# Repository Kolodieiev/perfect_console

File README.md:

Проєкт “Ідеальна консоль” це спроба створити універсальну електронну плату, для комфортного програмування на її основі різноманітних електронних пристроїв, таких як ігрові консолі, програвачі музики, пульти керування тощо.
Завдяки продуктивному мікроконтролеру ESP32S3 N16R8 плата може виконувати купу завдань та обчислень, а наявність 8 мб оперативної та 16 мб постійної пам'яті, забезпечує достатньо місця для реалізації досить об’ємних проєктів прошивок, в тому числі з використанням графіки. 

<br>

#### Прошивка
В репозиторії, крім файлів проєкту електронної плати, містяться повністю відкриті базові прошивки, написані мовою C++, для обох мікроконтролерів. Прошивка для ESP32S3 базується на основі фреймворку Pixeler, та містить багато прикладів побудови графічного інтерфейсу різної складності. 
До їх списку входять різні види меню, графічний інтерфейс для сканування та підключення до WiFi точки доступу, файловий менеджер, mp3-плеєр, вікна з різними видами налаштувань, приклади 2D-ігор на кастомному ігровому рушії та інші.

Скриншоти з прошивки:<br>

<br>

<br>
Демонстрація можливостей ігрового рушія(зібрано в портованій версії для ПК):
<br>

<br>
Більше скриншотів можна знайти в [Screenshots](resources/images/screenshot)
<br>

#### Для кого
Проєкт розрахований на користувачів, які хочуть навчитися виготовляти або замовляти виготовлення електронних плат, збирати їх по схемі та програмувати мікроконтролери. Також він підійде досвідченим розробникам, яким просто цікаво програмувати залізо у вільний час та вивчати щось нове для себе. 
Для збірки проєкту необхідно мати досвід пайки середнього або вище рівня та відповідні інструменти.

<br>

#### Модульність
Головна особливість плати полягає в тому, що користувач може самостійно обрати, який модуль йому використовувати для своїх задач. На платі передбачено місця тільки для основних компонентів, або таких, які складно закріпити в корпусі окремо, все інше необхідно самостійно обирати з огляду на власні потреби та можливості.
<br>
<br>
[Фото зібраних плат](resources/images/pcb)

<br>

#### Корпус
Розробка корпусу для виготовлення на 3D-принтері не планується в межах даного проєкту. Користувач повинен самостійно спроектувати корпус для свого пристрою в залежності від використаних модулів. 

<br>

#### Мікроконтролер
Для забезпечення функціонування плати використовується два мікроконтролера - далі МК, ESP32S3 та CH32V006E8R6. Ці МК обрано через дуже хороше співвідношення ціна/можливості та значну кількість GPIO. Очікується, що перший МК буде мозком пристрою, який виконуватиме основну прошивку, а другий - допоміжний, що виконуватиме роль мікросхеми розширення, завдяки якій вивільняються 11 пінів основного МК. Мікроконтролери можуть спілкуватися один з одним по шині I2C. Для підтримки рівноправного двостороннього зв'язку додано окрему лінію між МК, яка може бути використана для генерації переривань.

<br>

#### GPIO
До однієї з двох шин SPI на ESP32 приєднано роз’єм карти пам’яті MicroSD. Усі інші незадіяні виводи цього МК виведено на штирьові роз’єми та контактні площадки. Усього доступно вільних пінів 19 + шина I2C + UART. Усі вільні виводи ESP32 згруповано на штирьових роз’ємах таким чином, щоб до них можна було підключити з допомогою шлейфів будь-який популярний SPI-дисплей, модуль звуку, який керується по I2S протоколу, цифровий мікрофон та UART-версію модулів LoRa. До кожної групи роз’ємів додано піни живлення, які вмикаються польовими транзисторами. В кастомній прошивці до цих роз’ємів можуть бути підключені будь-які інші модулі на розсуд користувача.

Частина виводів(п’ять) CH32 підключені до ключів керування живленням. Усі інші піни також виведені на штирьові роз’єми. У стандартній конфігурації до цих пінів очікується підключення кнопки живлення, кнопки PTT, ліній UART, програматора, та 8 кнопок керування, 6 з яких, можуть бути налаштовані як сенсорні. 

В будь-якій користувацькій конфігурації обов’язковою є тільки кнопка живлення. Усі інші вільні виводи мікроконтролерів можуть бути налаштовані, відповідно до їх документації, на інші задачі. Окрім того, за особливої необхідності, можуть бути звільнені додаткові 4 піна CH32, які підключені до затворів ключів живлення в кожній групі штирьових роз’ємів.

<br>

#### Живлення
Очікується, що плата “Ідеальної консолі” буде використовуватися саме в автономному варіанті з використанням високоємнісного акумулятора або збірки акумуляторів. Проте з деякими незначними модифікаціями можливе її використання виключно в стаціонарному варіанті, наприклад, для навчання або відлагодження. На платі передбачено місця для штирьових роз’ємів, до яких можна підключити будь-який USB роз’єм, та будь-який понижуючий DC-DC перетворювач. Також окремо виведено роз’єм з підсиленими доріжками для живлення зовнішніх пристроїв, як від DC-DC перетворювача, так і напряму від акумулятора. Для заряджання акумулятора використовується модуль TP4056 без захисту. Для нього передбачено окреме місце на платі для відводу тепла. Плату або плати захисту від перерозряду пропонується встановлювати окремо на акумулятор в залежності від того, які значення струму планується знімати з нього. Якщо очікується загальне споживання струму понад 1А, дуже рекомендується припаювання проводів до плати, замість використання штирьових роз’ємів в схемі живлення.

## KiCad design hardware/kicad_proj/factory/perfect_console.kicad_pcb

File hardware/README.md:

##### Загальні рекомендації

* Не запаюйте акумулятор та DC-DC перетворювач безпосередньо до плати, поки не завантажите прошивку на CH32V006E8R6.
* Не приєднуйте жоден із модулів, таких як дисплей, до плати та не вставляйте карту пам'яті в роз'єм, доки не переконаєтесь, що на платі відсутні КЗ, а обидва мікроконтролери успішно прошиті.
* Мікроконтролер CH32V006E8R6 не може бути замінений на будь-яку інший з серії через невідповідність пінів.
* Модуль ESP32-S3 не може бути замінений на звичайний ESP32 чи S2 чи будь-який інший через невідповідність пінів та підтримку можливостей.
* Шлейф дисплею мусить бути якомога коротшим, настільки дозволяють вимоги корпусу. 
* Резистори підтяжки ліній MISO/MOSI/CLK карти пам'яті можуть мати значення 10-22к. 
* Резистори підтяжки затворів мосфетів можуть мати значення 30к-50к.
* Резистори обмеження струму на затвори мосфетів можуть мати значення 10-30ом.
* Конденсатори 10мкф можуть бути замінені на low-esr електролітичні або танталові, але з урахуванням полярності.
* DC-DC перетворювач може бути використаний будь-який на 3.3В 1.5А+. Рекомендованими є XL63070/TPS63070/mini-560 3.3v.
* Захист акумулятора від перерозряду, КЗ та високих струмів необхідно купити окремо з розрахунку 1 модуль на 2А потенційного струму.
* Якщо планується використання підсилювача звуку або модуля LoRa, рекомендуються купувати високострумний акумулятор та з'єднати паралельно два модуля захисту.
* Під модуль TP4056 рекомендується розмістити термопрокладку для відводу тепла на плату.
* Для комфортного використання плати рекомендується купувати акумулятор з ємністю від 1000маг. Бажано 2-3к, якщо планується використання WiFi. Найкраще для цієї задачі підходять високострумні 18650 або 21700 зі встановленими самостійно модулями захисту.
* Під модуль ESP32-S3 бажано нанести маленьку каплю процесорної термопасти і міцно притиснути модуль до плати, якщо паста густа, можна легко порухати модуль в різні сторони, для кращого розмазування термопасти. 
* Запаювати площадку знизу не обов'язково і не рекомендуються новачкам.
* Дисплей може бути використаний будь-який SPI, але основна прошивка буде розроблюватися тільки для дисплеїв на драйвері ST7789.
* Модуль мікрофона, якщо планується його використання, може бути замінений на будь-який інший сумісний з INMP441.
* Модуль LoRa може бути використаний серії E32 або E220 з UART на 400-440мГц. Інші не тестувались та не мають бібліотек підтримки. 
* Усі модулі не є обов'язковими для функціонування плати, окрім модулів живлення, мікроконтролерів та їх обв'язки.

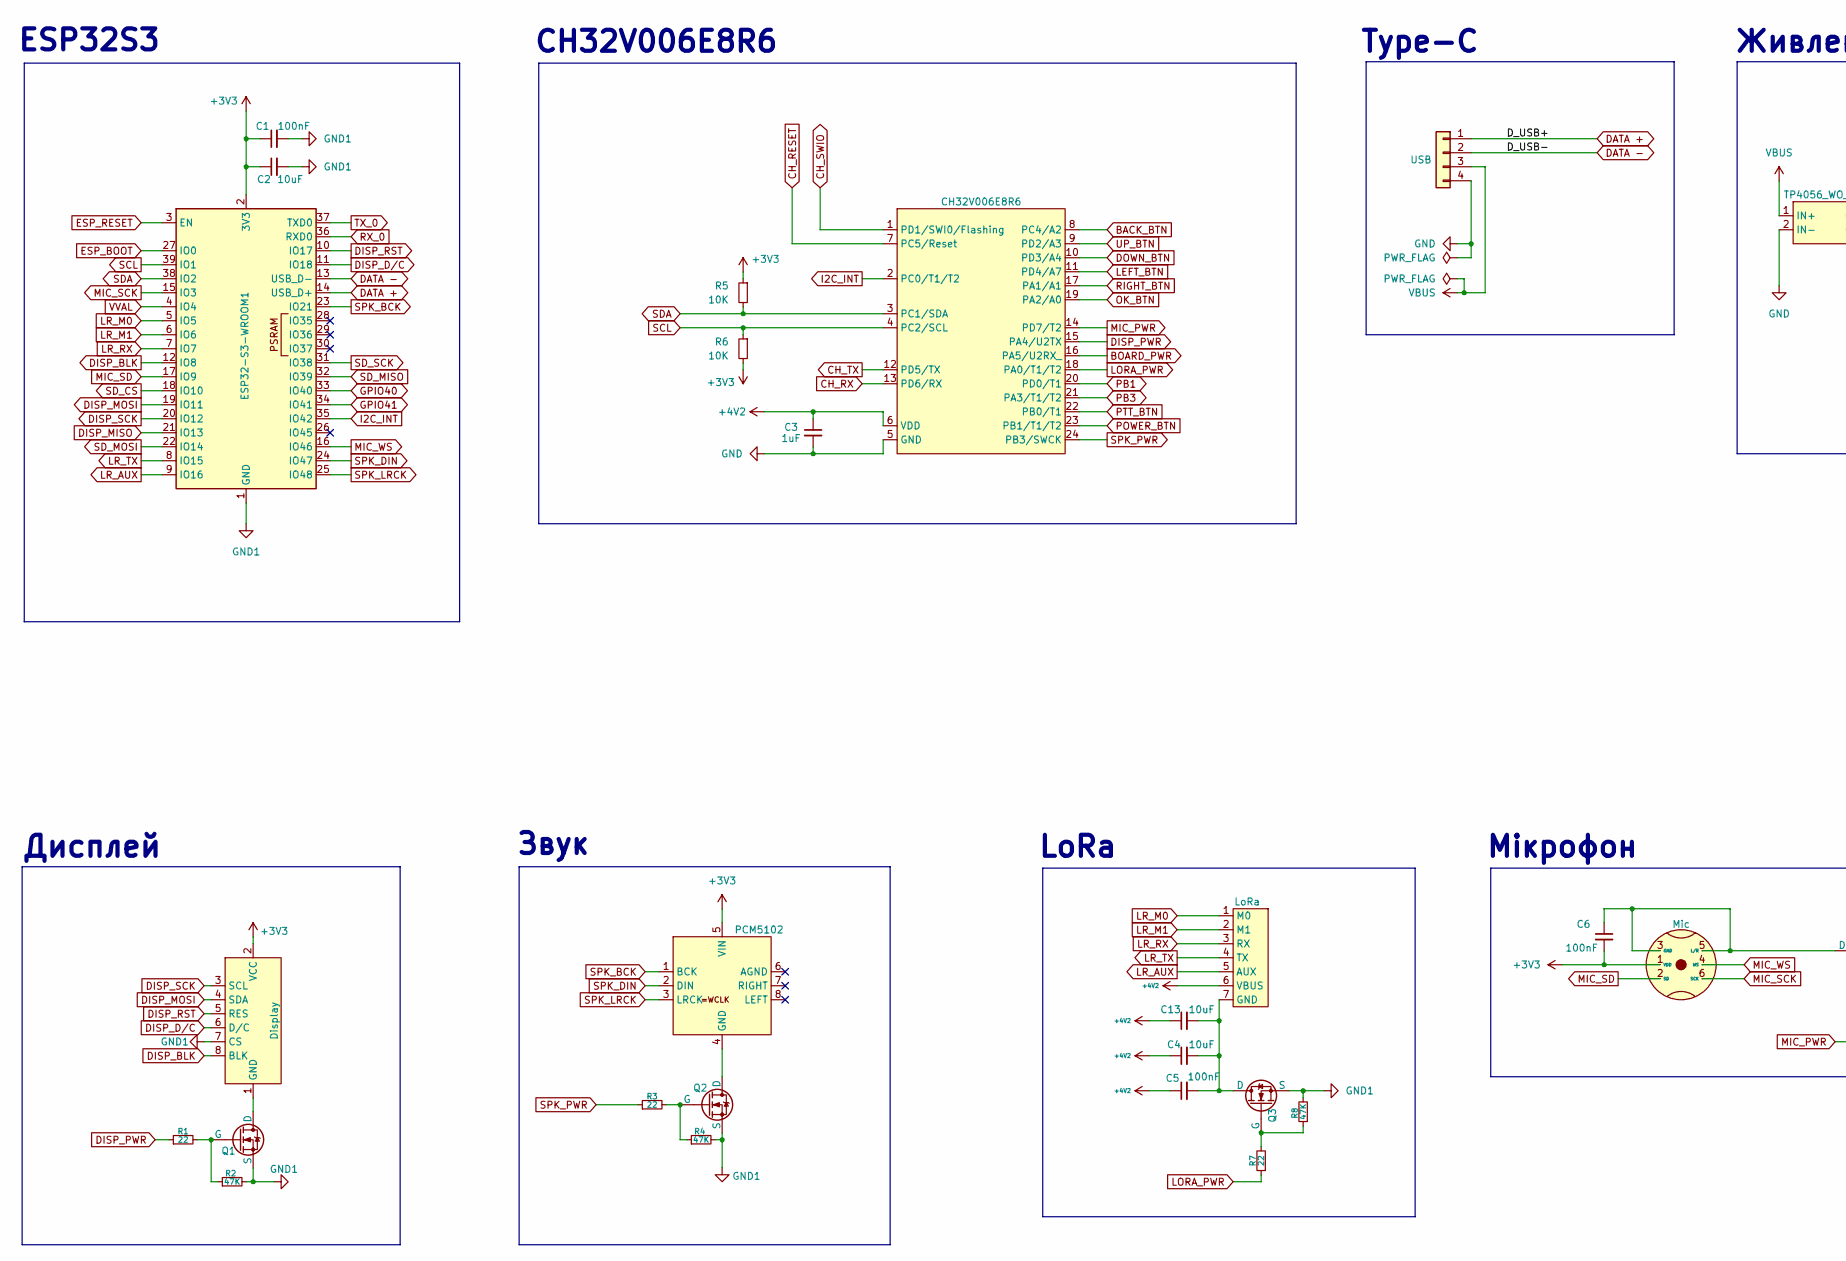
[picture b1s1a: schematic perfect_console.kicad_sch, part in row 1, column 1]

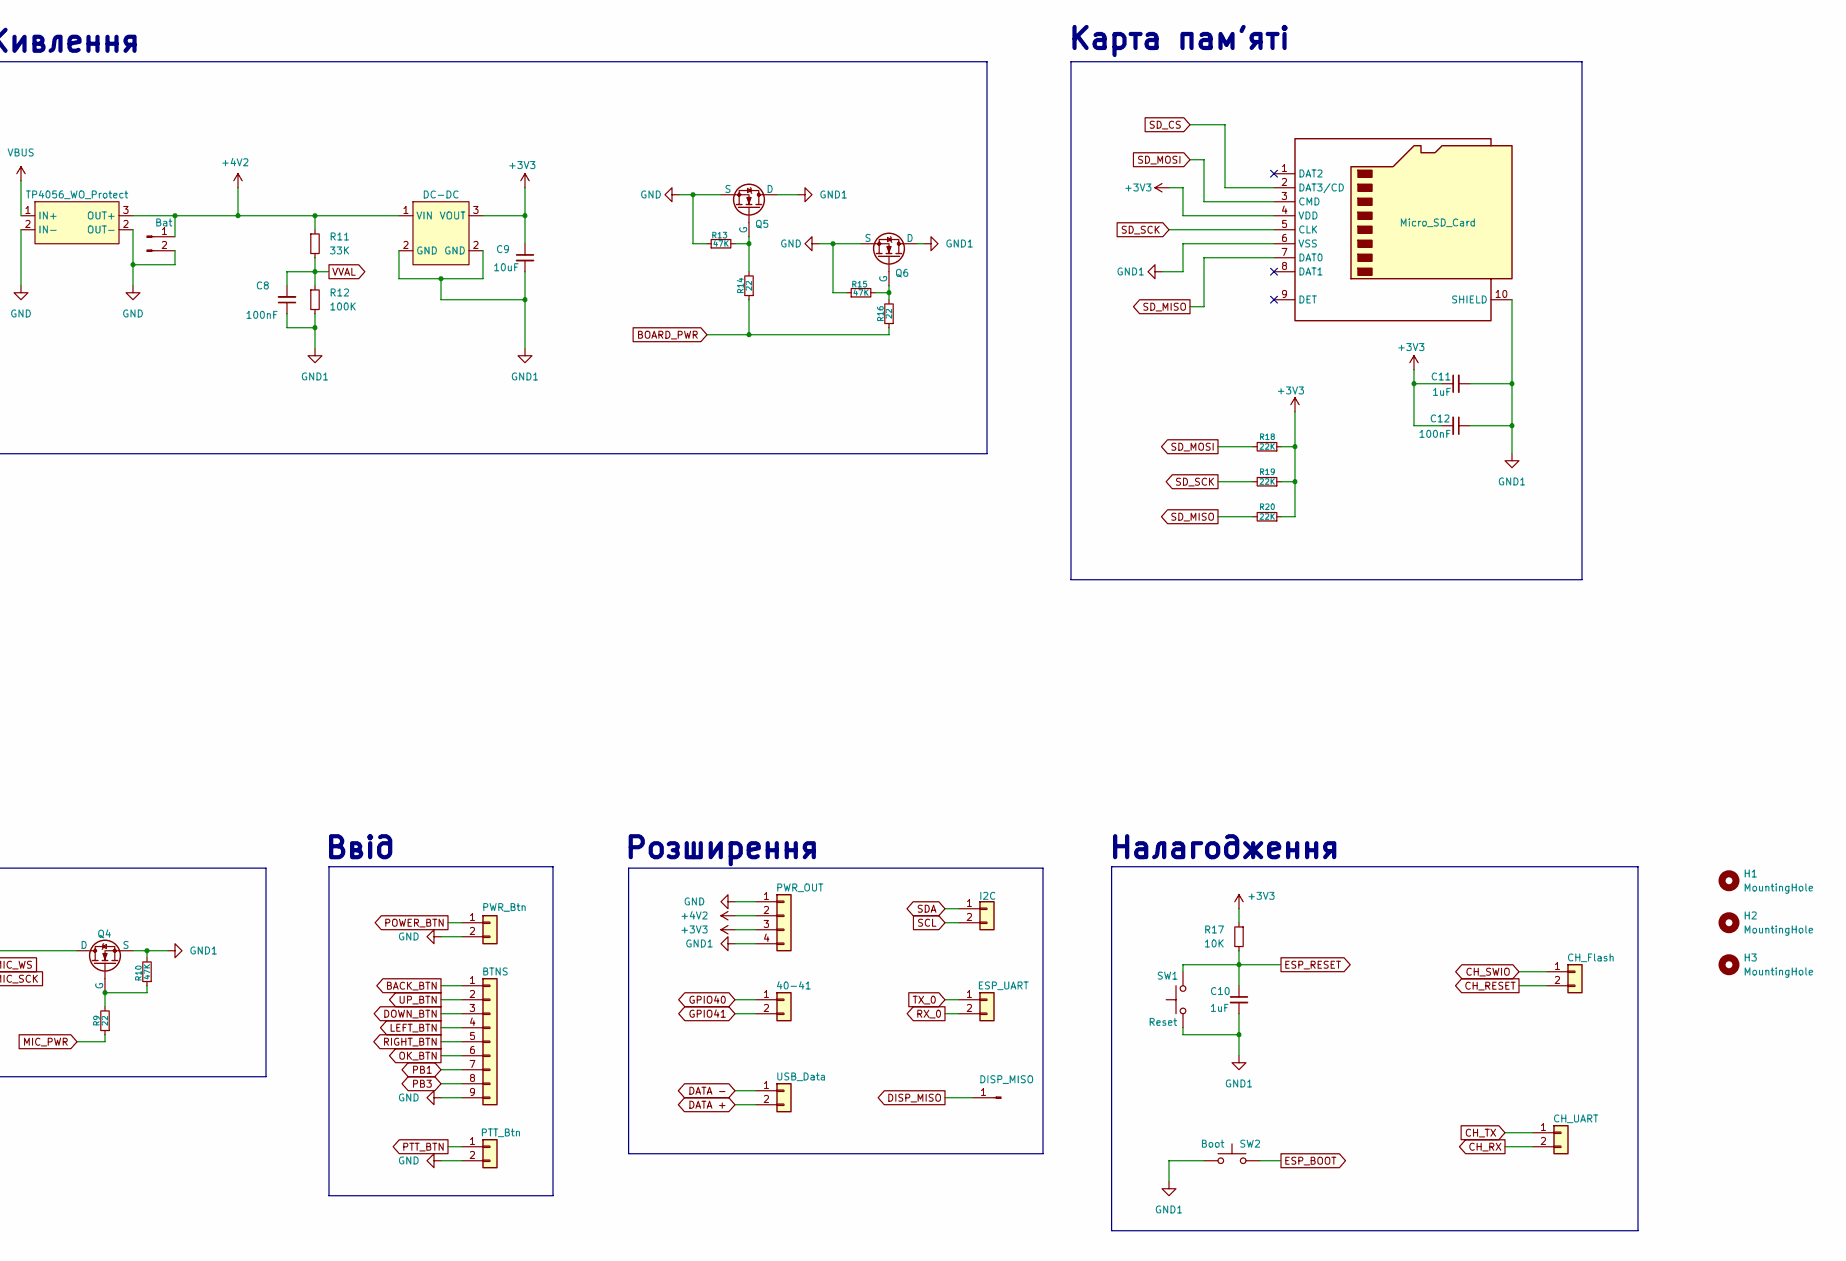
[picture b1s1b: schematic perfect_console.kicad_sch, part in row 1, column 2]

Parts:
C1, C5, C6, C8, C12: 100nF; C_1206_3216Metric_Pad1.33x1.80mm_HandSolder
C2, C4, C9, C13: 10uF; C_1206_3216Metric_Pad1.33x1.80mm_HandSolder
C3, C10, C11: 1uF; C_1206_3216Metric_Pad1.33x1.80mm_HandSolder
H1, H2, H3: MountingHole; MountingHole_2.7mm_M2.5_DIN965_Pad
J1: USB; PinHeader_1x04_P2.54mm_Vertical
J2: TP4056_WO_Protect; Charge_Controller_TP4056_WO_Protect
J3: Bat; PinHeader_1x02_P2.54mm_Vertical
J4: PWR_Btn; PinHeader_1x02_P2.54mm_Vertical
J5: BTNS; PinHeader_1x09_P2.54mm_Vertical
J6: PTT_Btn; PinHeader_1x02_P2.54mm_Vertical
J7: PWR_OUT; PinHeader_1x04_P2.54mm_Vertical
J8: 40-41; PinHeader_1x02_P2.54mm_Vertical
J9: USB_Data; PinHeader_1x02_P2.54mm_Vertical
J10: I2C; PinHeader_1x02_P2.54mm_Vertical
J11: ESP_UART; PinHeader_1x02_P2.54mm_Vertical
J12: CH_UART; PinHeader_1x02_P2.54mm_Vertical
J13: CH_Flash; PinHeader_1x02_P2.54mm_Vertical
J14: Micro_SD_Card; J_SD_Card-micro_socket_A
J16: DISP_MISO; TestPoint_Pad_1.5x1.5mm
Q1, Q2, Q3, Q4, Q5, Q6: A09T; SOT-23
R1, R3, R7, R9, R14, R16: 22; R_1206_3216Metric_Pad1.30x1.75mm_HandSolder
R2, R4, R8, R10, R13, R15: 47K; R_1206_3216Metric_Pad1.30x1.75mm_HandSolder
R5, R6, R17: 10K; R_1206_3216Metric_Pad1.30x1.75mm_HandSolder
R11: 33K; R_1206_3216Metric_Pad1.30x1.75mm_HandSolder
R12: 100K; R_1206_3216Metric_Pad1.30x1.75mm_HandSolder
R18, R19, R20: 22K; R_1206_3216Metric_Pad1.30x1.75mm_HandSolder
SW1: Reset; SW_PUSH_6mm
SW2: Boot; SW_PUSH_6mm
U1: ESP32-S3-WROOM1; ESP32-S3-WROOM-1
U2: Display; PinHeader_1x08_P2.54mm_Vertical
U3: PCM5102; PinHeader_1x05_P2.54mm_Vertical
U4: CH32V006E8R6; Allegro_QSOP-24_3.9x8.7mm_P0.635mm
U5: LoRa; PinHeader_1x07_P2.54mm_Vertical
U7: Mic; PinHeader_2x03_P2.54mm_Vertical
U8: DC-DC; PinHeader_2x02_P2.54mm_Vertical

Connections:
+3V3: C1.1, C2.1, C6.2, C9.1, C11.1, C12.2, J7.3, J14.4 (VDD), R5.1, R6.2, R17.1, R18.1, R19.1, R20.1, U1.2 (3V3), U2.2 (VCC), U3.5 (VIN), U7.1 (VDD), U8.3 (VOUT)
+4V2: C3.1, C4.1, C5.1, C13.1, J2.3 (OUT+), J3.1, J7.2, R11.1, U4.6 (VDD), U5.6 (VBUS), U8.1 (VIN)
BACK_BTN: J5.1, U4.8 (PC4/A2)
BOARD_PWR: R14.1, R16.1, U4.16 (PA5/U2RX_)
CH_RESET: J13.2, U4.7 (PC5/Reset)
CH_RX: J12.2, U4.13 (PD6/RX)
CH_SWIO: J13.1, U4.1 (PD1/SWI0/Flashing)
CH_TX: J12.1, U4.12 (PD5/TX)
DATA +: J1.1, J9.2, U1.14 (USB_D+)
DATA -: J1.2, J9.1, U1.13 (USB_D-)
DISP_BLK: U1.12 (IO8), U2.8 (BLK)
DISP_D/C: U1.11 (IO18), U2.6 (D/C)
DISP_MISO: J16.1, U1.21 (IO13)
DISP_MOSI: U1.19 (IO11), U2.4 (SDA)
DISP_PWR: R1.1, U4.15 (PA4/U2TX)
DISP_RST: U1.10 (IO17), U2.5 (RES)
DISP_SCK: U1.20 (IO12), U2.3 (SCL)
DOWN_BTN: J5.3, U4.10 (PD3/A4)
ESP_BOOT: SW2.2, U1.27 (IO0)
ESP_RESET: C10.1, R17.2, SW1.2, U1.3 (EN)
GND: C3.2, J1.4, J2.2 (IN-), J3.2, J4.2, J5.9, J6.2, J7.1, Q5.2 (S), Q6.2 (S), R13.1, R15.1, U4.5 (GND)
GND1: C1.2, C2.2, C8.1, C9.2, C10.2, C11.2, C12.1, J7.4, J14.6 (VSS), J14.10 (SHIELD), Q1.2 (S), Q2.2 (S), Q3.2 (S), Q4.2 (S), Q5.3 (D), Q6.3 (D), R2.2, R4.2, R8.2, R10.2, R12.2, SW1.1, SW2.1, U1.1 (GND), U1.40 (GND), U1.41 (GND), U2.7 (CS), U8.2 (GND)
GPIO40: J8.1, U1.33 (IO40)
GPIO41: J8.2, U1.34 (IO41)
I2C_INT: U1.35 (IO42), U4.2 (PC0/T1/T2)
LEFT_BTN: J5.4, U4.11 (PD4/A7)
LORA_PWR: R7.1, U4.18 (PA0/T1/T2)
LR_AUX: U1.9 (IO16), U5.5 (AUX)
LR_M0: U1.5 (IO5), U5.1 (M0)
LR_M1: U1.6 (IO6), U5.2 (M1)
LR_RX: U1.7 (IO7), U5.3 (RX)
LR_TX: U1.8 (IO15), U5.4 (TX)
MIC_PWR: R9.1, U4.14 (PD7/T2)
MIC_SCK: U1.15 (IO3), U7.6 (SCK)
MIC_SD: U1.17 (IO9), U7.2 (SD)
MIC_WS: U1.16 (IO46), U7.4 (WS)
unnamed: Q1.3 (D), U2.1 (GND)
unnamed: Q1.1 (G), R1.2, R2.1
unnamed: Q2.3 (D), U3.4 (GND)
unnamed: Q2.1 (G), R3.2, R4.1
unnamed: C4.2, C5.2, C13.2, Q3.3 (D), U5.7 (GND)
unnamed: Q3.1 (G), R7.2, R8.1
unnamed: C6.1, Q4.3 (D), U7.3 (GND), U7.5 (L/R)
unnamed: Q4.1 (G), R9.2, R10.1
unnamed: Q5.1 (G), R13.2, R14.2
unnamed: Q6.1 (G), R15.2, R16.2
OK_BTN: J5.6, U4.19 (PA2/A0)
PB1: J5.7, U4.20 (PD0/T1)
PB3: J5.8, U4.21 (PA3/T1/T2)
POWER_BTN: J4.1, U4.23 (PB1/T1/T2)
PTT_BTN: J6.1, U4.22 (PB0/T1)
RIGHT_BTN: J5.5, U4.17 (PA1/A1)
RX_0: J11.2, U1.36 (RXD0)
SCL: J10.2, R6.1, U1.39 (IO1), U4.4 (PC2/SCL)
SDA: J10.1, R5.2, U1.38 (IO2), U4.3 (PC1/SDA)
SD_CS: J14.2 (DAT3/CD), U1.18 (IO10)
SD_MISO: J14.7 (DAT0), R20.2, U1.32 (IO39)
SD_MOSI: J14.3 (CMD), R18.2, U1.22 (IO14)
SD_SCK: J14.5 (CLK), R19.2, U1.31 (IO38)
SPK_BCK: U1.23 (IO21), U3.1 (BCK)
SPK_DIN: U1.24 (IO47), U3.2 (DIN)
SPK_LRCK: U1.25 (IO48), U3.3 (LRCK)
SPK_PWR: R3.1, U4.24 (PB3/SWCK)
TX_0: J11.1, U1.37 (TXD0)
UP_BTN: J5.2, U4.9 (PD2/A3)
VBUS: J1.3, J2.1 (IN+)
VVAL: C8.2, R11.2, R12.1, U1.4 (IO4)

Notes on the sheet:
Розширення
Карта пам'яті
Налагодження
Дисплей
CH32V006E8R6
Живлення
Звук
Type-C
ESP32S3
Ввід
LoRa
Мікрофон

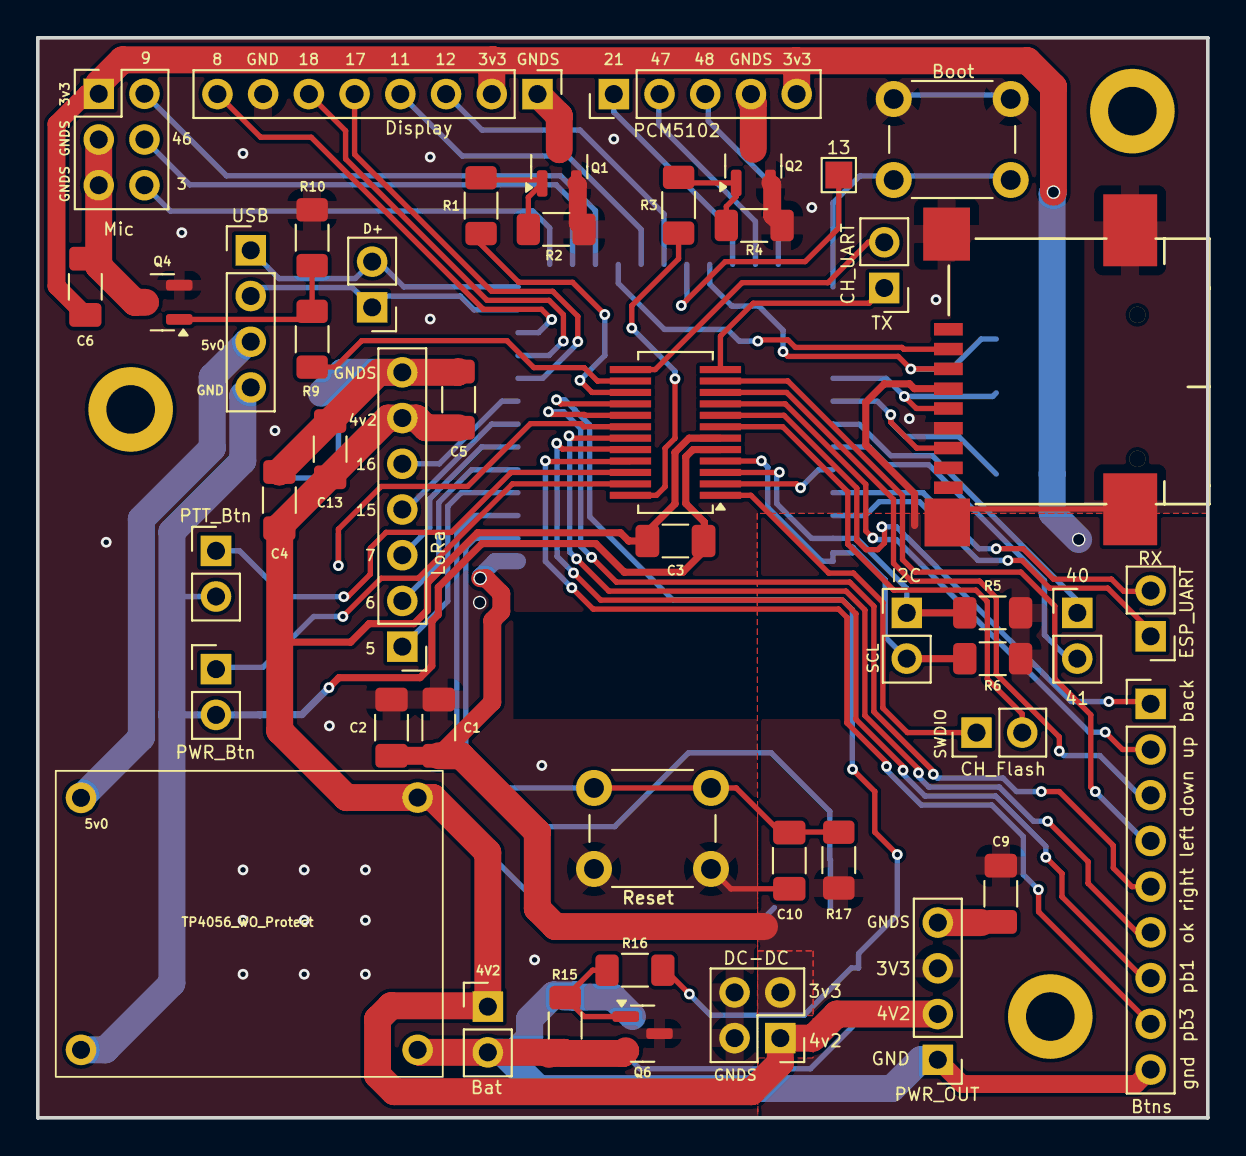
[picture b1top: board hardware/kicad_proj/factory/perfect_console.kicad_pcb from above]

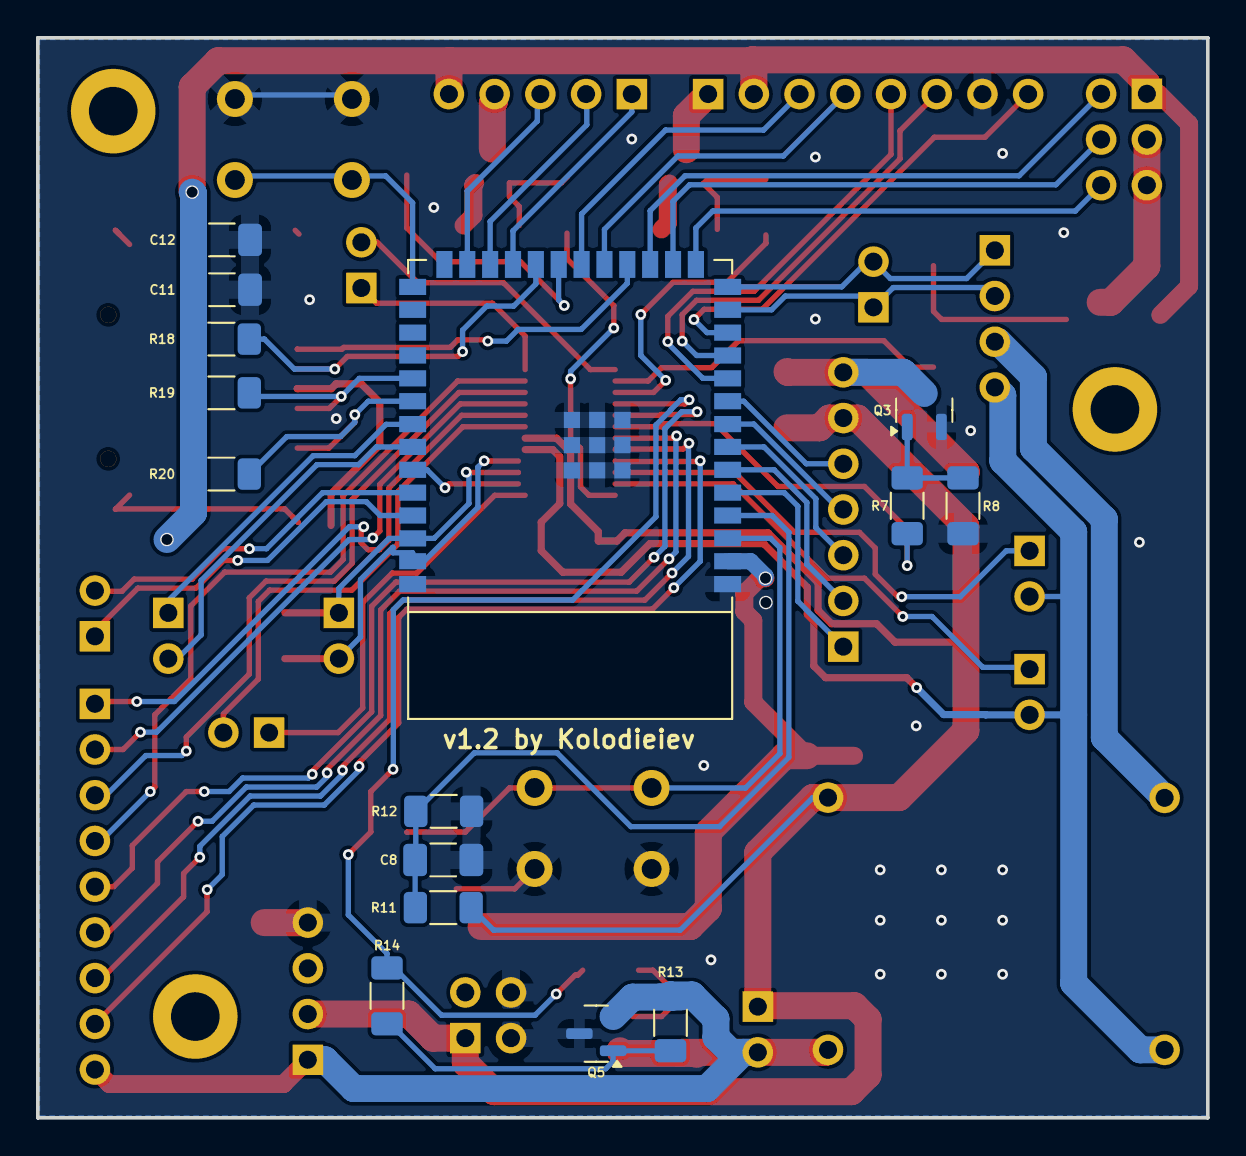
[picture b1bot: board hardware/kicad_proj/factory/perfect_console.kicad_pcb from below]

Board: 2 copper layers, 65.0 x 60.0 mm, 65 parts (15 on the bottom side), 67 nets.

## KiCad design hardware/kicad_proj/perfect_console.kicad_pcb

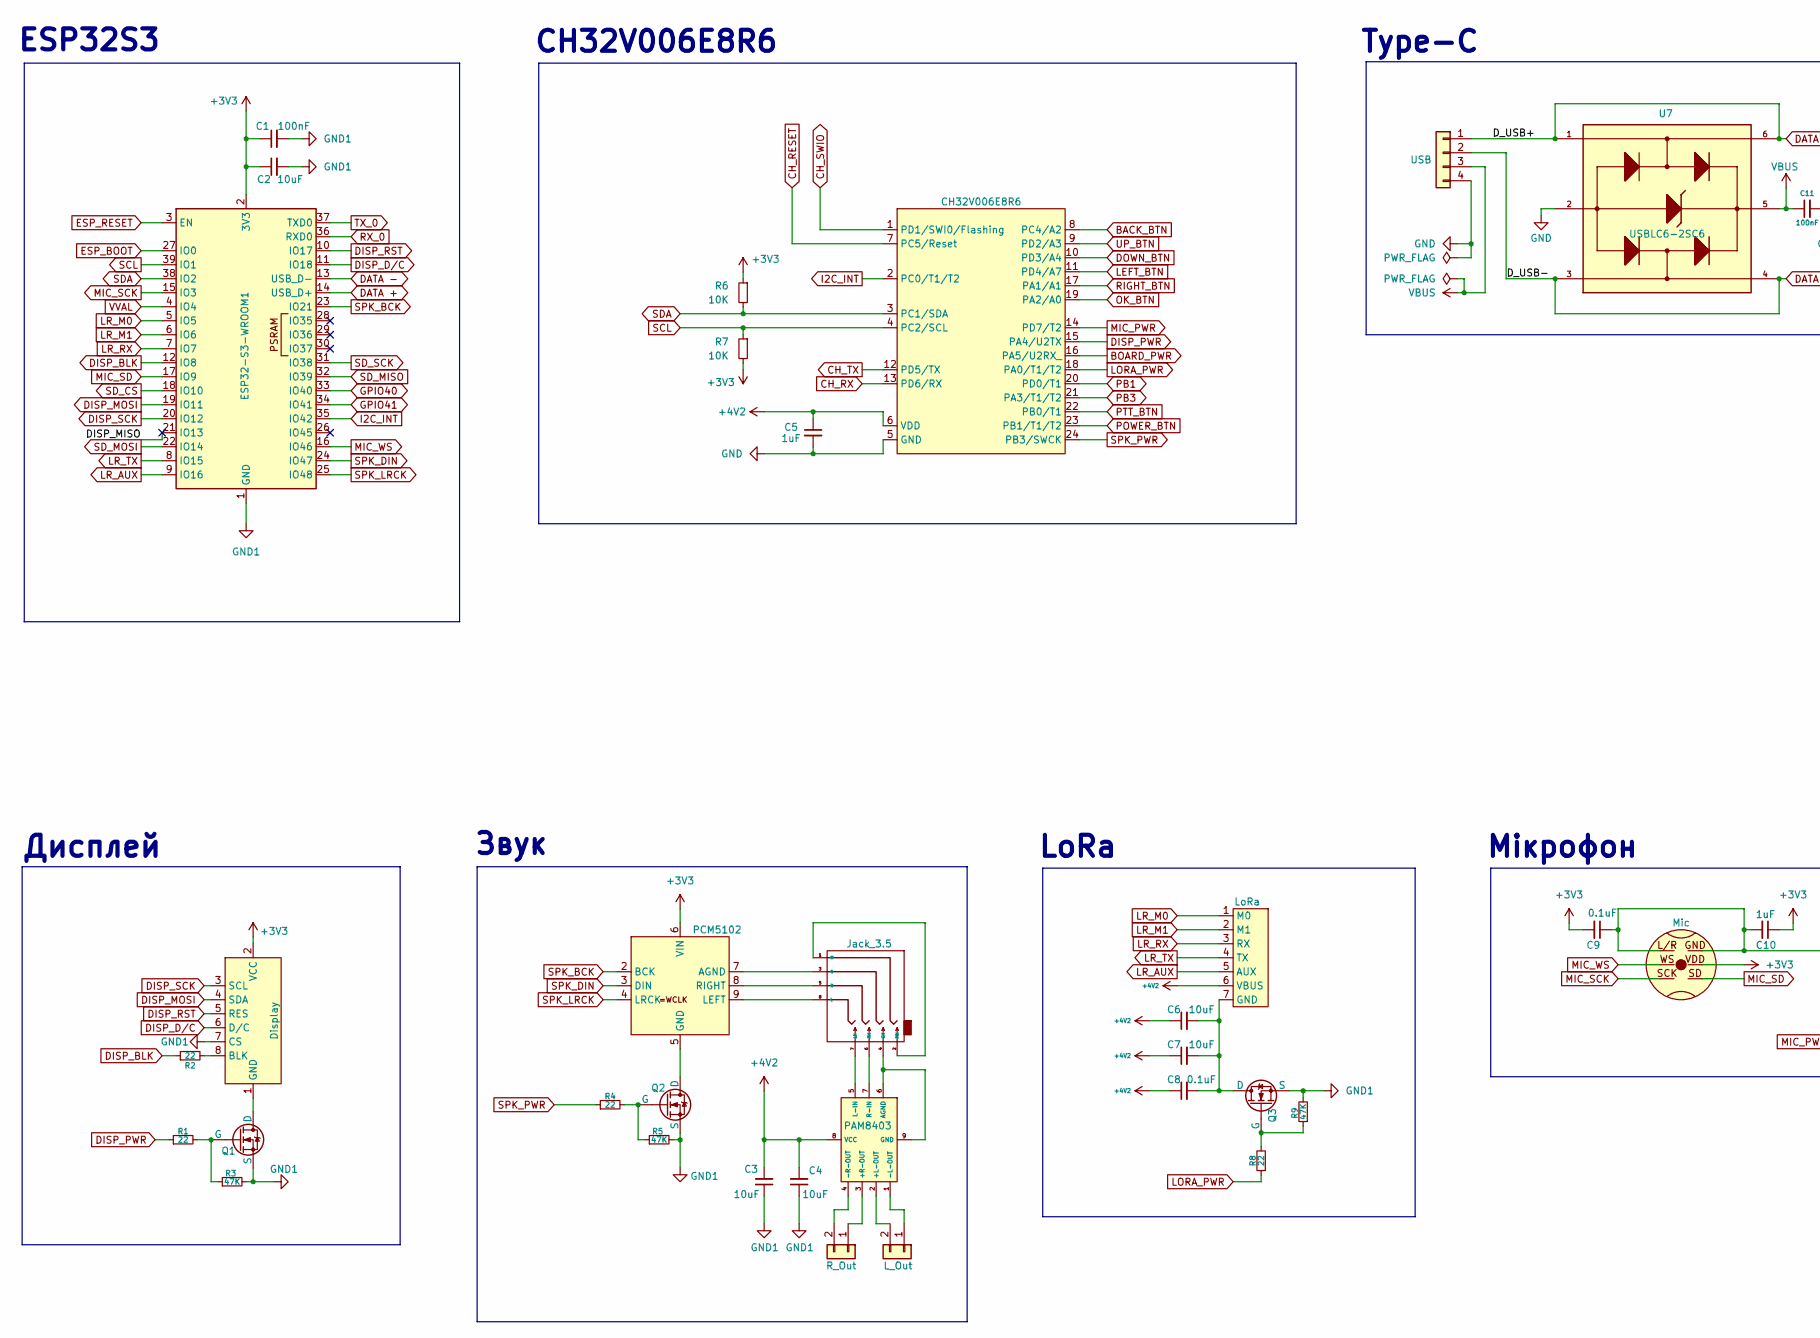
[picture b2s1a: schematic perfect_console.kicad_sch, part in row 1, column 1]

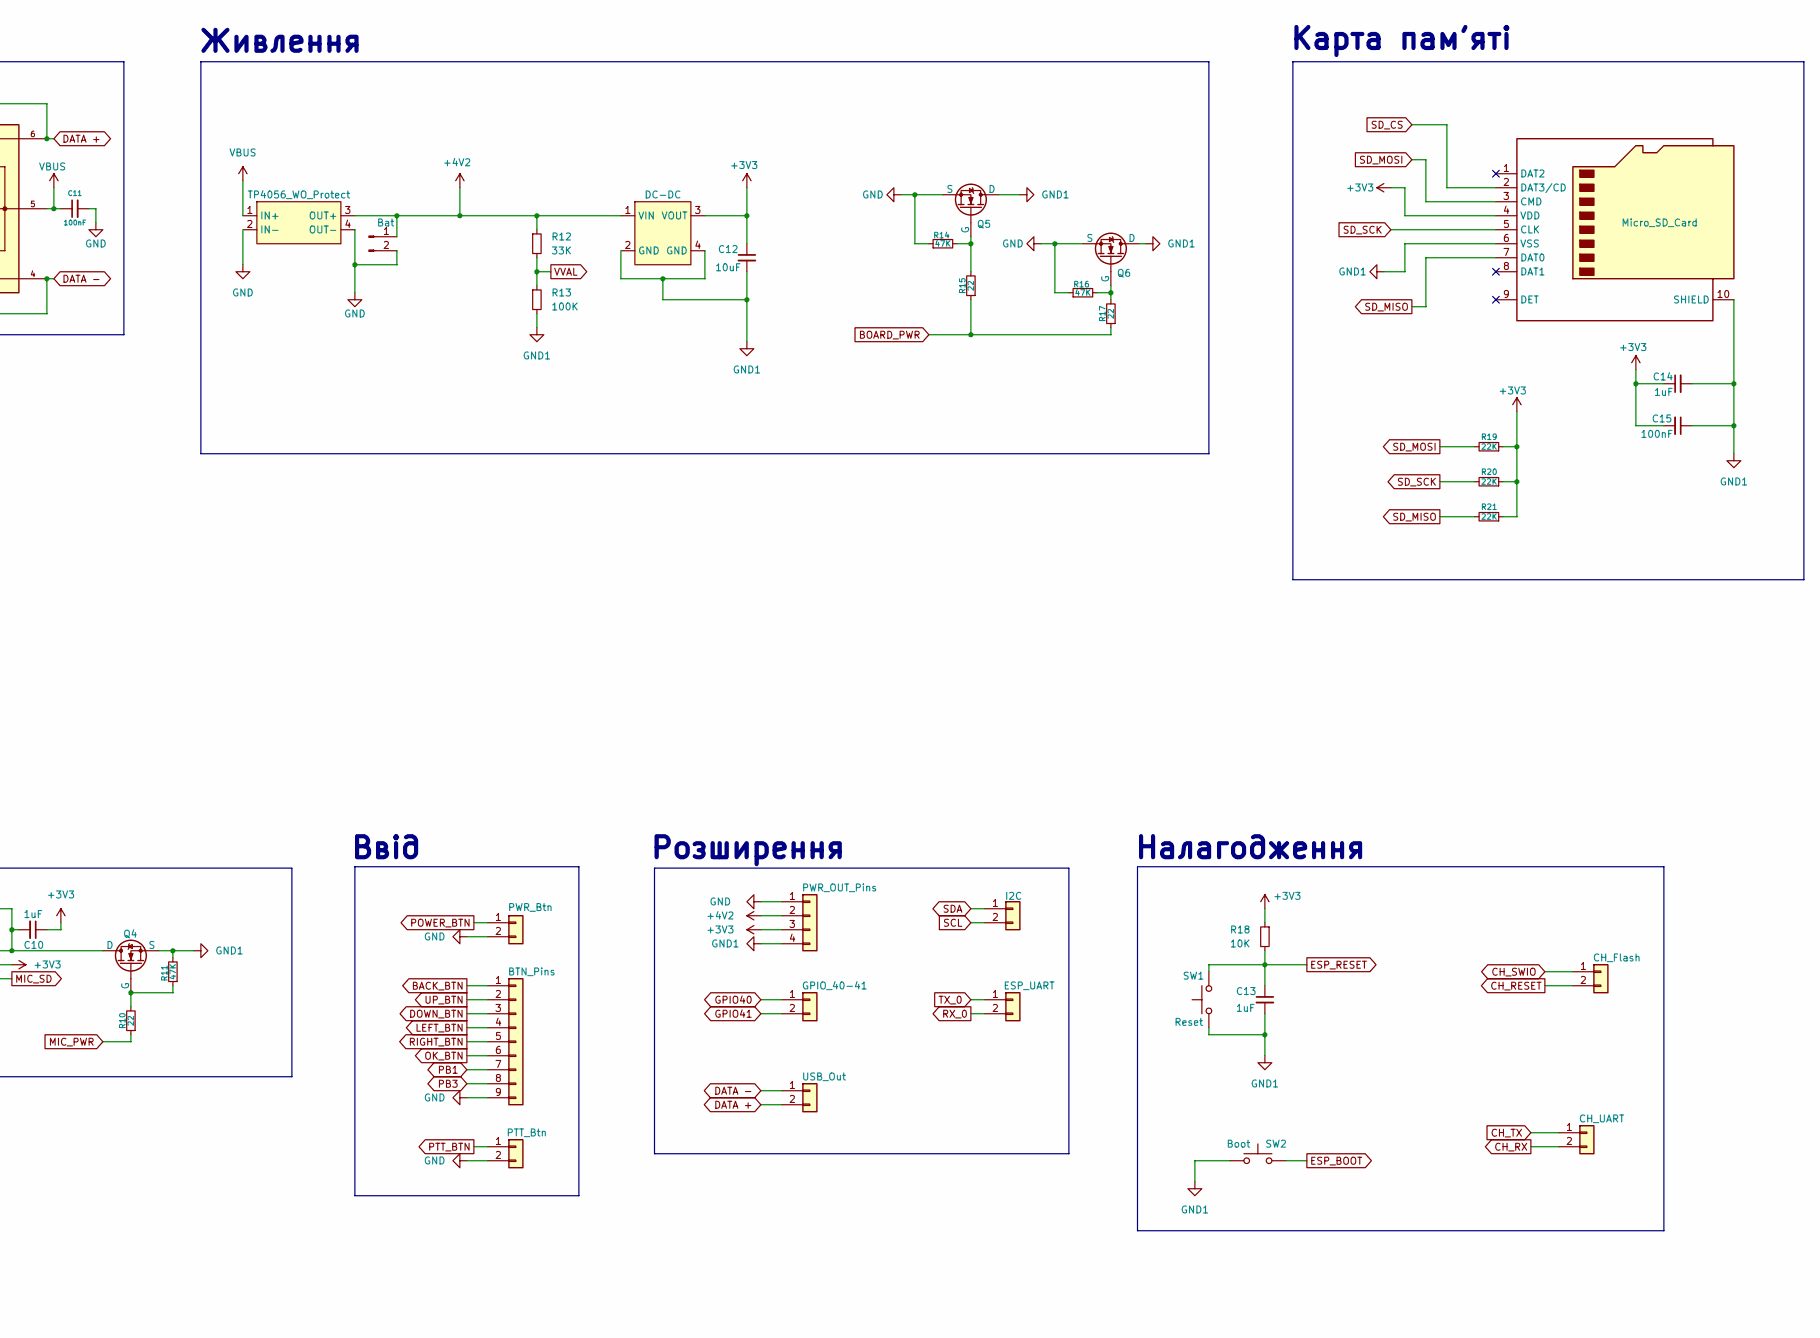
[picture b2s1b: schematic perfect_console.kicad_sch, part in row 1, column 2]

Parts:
C1, C11, C15: 100nF; C_1206_3216Metric
C2, C3, C4, C6, C7, C12: 10uF; C_1206_3216Metric
C5, C10, C13, C14: 1uF; C_1206_3216Metric
C8, C9: 0.1uF; C_1206_3216Metric
J1: R_Out; PinHeader_1x02_P2.54mm_Vertical
J2: Jack_3.5; PJ-393_8PJ
J3: L_Out; PinHeader_1x02_P2.54mm_Vertical
J4: USB; PinHeader_1x04_P2.54mm_Vertical
J5: TP4056_WO_Protect; Charge_Controller_TP4056_WO_Protect
J6: Bat; PinHeader_1x02_P2.54mm_Vertical
J7: PWR_Btn; PinHeader_1x02_P2.54mm_Vertical
J8: BTN_Pins; PinHeader_1x09_P2.54mm_Vertical
J9: PTT_Btn; PinHeader_1x02_P2.54mm_Vertical
J10: PWR_OUT_Pins; PinHeader_1x04_P2.54mm_Vertical
J11: GPIO_40-41; PinHeader_1x02_P2.54mm_Vertical
J12: USB_Out; PinHeader_1x02_P2.54mm_Vertical
J13: I2C; PinHeader_1x02_P2.54mm_Vertical
J14: ESP_UART; PinHeader_1x02_P2.54mm_Vertical
J16: CH_UART; PinHeader_1x02_P2.54mm_Vertical
J17: CH_Flash; PinHeader_1x02_P2.54mm_Vertical
J18: Micro_SD_Card; J_SD_Card-micro_socket_A
Q1, Q2, Q3, Q4, Q5, Q6: NMOS; SOT-23
R1, R2, R4, R8, R10, R15, R17: 22; R_1206_3216Metric_Pad1.30x1.75mm_HandSolder
R3, R5, R9, R11, R14, R16: 47K; R_1206_3216Metric_Pad1.30x1.75mm_HandSolder
R6, R7, R18: 10K; R_1206_3216Metric_Pad1.30x1.75mm_HandSolder
R12: 33K; R_1206_3216Metric_Pad1.30x1.75mm_HandSolder
R13: 100K; R_1206_3216Metric_Pad1.30x1.75mm_HandSolder
R19, R20, R21: 22K; R_1206_3216Metric_Pad1.30x1.75mm_HandSolder
SW1: Reset; SW_PUSH_6mm
SW2: Boot; SW_PUSH_6mm
U1: ESP32-S3-WROOM1; ESP32-S3-WROOM-1
U2: Display; PinHeader_1x08_P2.54mm_Vertical
U3: PCM5102; PCM5102A-Module-Shortened
U4: CH32V006E8R6; Allegro_QSOP-24_3.9x8.7mm_P0.635mm
U5: PAM8403; PAM8403_Module
U6: LoRa; PinHeader_1x07_P2.54mm_Vertical
U7: USBLC6-2SC6; SOT-23-6
U8: Mic; INMP441_I2S_Module
U9: DC-DC; PinHeader_2x02_P2.54mm_Vertical

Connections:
+3V3: C1.1, C2.1, C9.2, C10.1, C12.1, C14.1, C15.2, J10.3, J18.4 (VDD), R6.1, R7.2, R18.1, R19.1, R20.1, R21.1, U1.2 (3V3), U2.2 (VCC), U3.6 (VIN), U8.VDD, U9.3 (VOUT)
+4V2: C3.2, C4.2, C5.1, C6.1, C7.1, C8.1, J5.3 (OUT+), J6.1, J10.2, R12.1, U4.6 (VDD), U5.8 (VCC), U6.6 (VBUS), U9.1 (VIN)
/DISP_MISO: U1.21 (IO13)
BACK_BTN: J8.1, U4.8 (PC4/A2)
BOARD_PWR: R15.1, R17.1, U4.16 (PA5/U2RX_)
CH_RESET: J17.2, U4.7 (PC5/Reset)
CH_RX: J16.2, U4.13 (PD6/RX)
CH_SWIO: J17.1, U4.1 (PD1/SWI0/Flashing)
CH_TX: J16.1, U4.12 (PD5/TX)
DATA +: J4.1, J12.2, U1.14 (USB_D+), U7.1, U7.6
DATA -: J4.2, J12.1, U1.13 (USB_D-), U7.3, U7.4
DISP_BLK: R2.1, U1.12 (IO8)
DISP_D/C: U1.11 (IO18), U2.6 (D/C)
DISP_MOSI: U1.19 (IO11), U2.4 (SDA)
DISP_PWR: R1.1, U4.15 (PA4/U2TX)
DISP_RST: U1.10 (IO17), U2.5 (RES)
DISP_SCK: U1.20 (IO12), U2.3 (SCL)
DOWN_BTN: J8.3, U4.10 (PD3/A4)
ESP_BOOT: SW2.2, U1.27 (IO0)
ESP_RESET: C13.1, R18.2, SW1.2, U1.3 (EN)
GND: C5.2, C11.2, J4.4, J5.2 (IN-), J5.4 (OUT-), J6.2, J7.2, J8.9, J9.2, J10.1, Q5.2 (S), Q6.2 (S), R14.1, R16.1, U4.5 (GND), U7.2
GND1: C1.2, C2.2, C3.1, C4.1, C12.2, C13.2, C14.2, C15.1, J10.4, J18.6 (VSS), J18.10 (SHIELD), Q1.2 (S), Q2.2 (S), Q3.2 (S), Q4.2 (S), Q5.3 (D), Q6.3 (D), R3.2, R5.2, R9.2, R11.2, R13.2, SW1.1, SW2.1, U1.1 (GND), U1.40 (GND), U1.41 (GND), U2.7 (CS), U9.2 (GND), U9.4 (GND)
GPIO40: J11.1, U1.33 (IO40)
GPIO41: J11.2, U1.34 (IO41)
I2C_INT: U1.35 (IO42), U4.2 (PC0/T1/T2)
LEFT_BTN: J8.4, U4.11 (PD4/A7)
LORA_PWR: R8.1, U4.18 (PA0/T1/T2)
LR_AUX: U1.9 (IO16), U6.5 (AUX)
LR_M0: U1.5 (IO5), U6.1 (M0)
LR_M1: U1.6 (IO6), U6.2 (M1)
LR_RX: U1.7 (IO7), U6.3 (RX)
LR_TX: U1.8 (IO15), U6.4 (TX)
MIC_PWR: R10.1, U4.14 (PD7/T2)
MIC_SCK: U1.15 (IO3), U8.SCK
MIC_SD: U1.17 (IO9), U8.SD
MIC_WS: U1.16 (IO46), U8.WS
unnamed: J1.1, U5.3 (+R-OUT)
unnamed: J1.2, U5.4 (-R-OUT)
unnamed: J2.3 (G), U3.7 (AGND)
unnamed: J2.4 (GN), U5.6 (AGND), U5.9 (GND)
unnamed: J2.8 (L), U3.9 (LEFT)
unnamed: J2.7 (LN), U5.5 (L-IN)
unnamed: J2.1 (M), J2.2 (MN)
unnamed: J2.5 (R), U3.8 (RIGHT)
unnamed: J2.6 (RN), U5.7 (R-IN)
unnamed: J3.1, U5.1 (-L-OUT)
unnamed: J3.2, U5.2 (+L-OUT)
unnamed: Q1.3 (D), U2.1 (GND)
unnamed: Q1.1 (G), R1.2, R3.1
unnamed: Q2.3 (D), U3.5 (GND)
unnamed: Q2.1 (G), R4.2, R5.1
unnamed: C6.2, C7.2, C8.2, Q3.3 (D), U6.7 (GND)
unnamed: Q3.1 (G), R8.2, R9.1
unnamed: C9.1, C10.2, Q4.3 (D), U8.GND, U8.L/R
unnamed: Q4.1 (G), R10.2, R11.1
unnamed: Q5.1 (G), R14.2, R15.2
unnamed: Q6.1 (G), R16.2, R17.2
unnamed: R2.2, U2.8 (BLK)
OK_BTN: J8.6, U4.19 (PA2/A0)
PB1: J8.7, U4.20 (PD0/T1)
PB3: J8.8, U4.21 (PA3/T1/T2)
POWER_BTN: J7.1, U4.23 (PB1/T1/T2)
PTT_BTN: J9.1, U4.22 (PB0/T1)
RIGHT_BTN: J8.5, U4.17 (PA1/A1)
RX_0: J14.2, U1.36 (RXD0)
SCL: J13.2, R7.1, U1.39 (IO1), U4.4 (PC2/SCL)
SDA: J13.1, R6.2, U1.38 (IO2), U4.3 (PC1/SDA)
SD_CS: J18.2 (DAT3/CD), U1.18 (IO10)
SD_MISO: J18.7 (DAT0), R21.2, U1.32 (IO39)
SD_MOSI: J18.3 (CMD), R19.2, U1.22 (IO14)
SD_SCK: J18.5 (CLK), R20.2, U1.31 (IO38)
SPK_BCK: U1.23 (IO21), U3.2 (BCK)
SPK_DIN: U1.24 (IO47), U3.3 (DIN)
SPK_LRCK: U1.25 (IO48), U3.4 (LRCK)
SPK_PWR: R4.1, U4.24 (PB3/SWCK)
TX_0: J14.1, U1.37 (TXD0)
UP_BTN: J8.2, U4.9 (PD2/A3)
VBUS: C11.1, J4.3, J5.1 (IN+), U7.5
VVAL: R12.2, R13.1, U1.4 (IO4)

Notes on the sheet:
Розширення
Карта пам'яті
Налагодження
Дисплей
CH32V006E8R6
Живлення
Звук
Type-C
ESP32S3
Ввід
LoRa
Мікрофон
